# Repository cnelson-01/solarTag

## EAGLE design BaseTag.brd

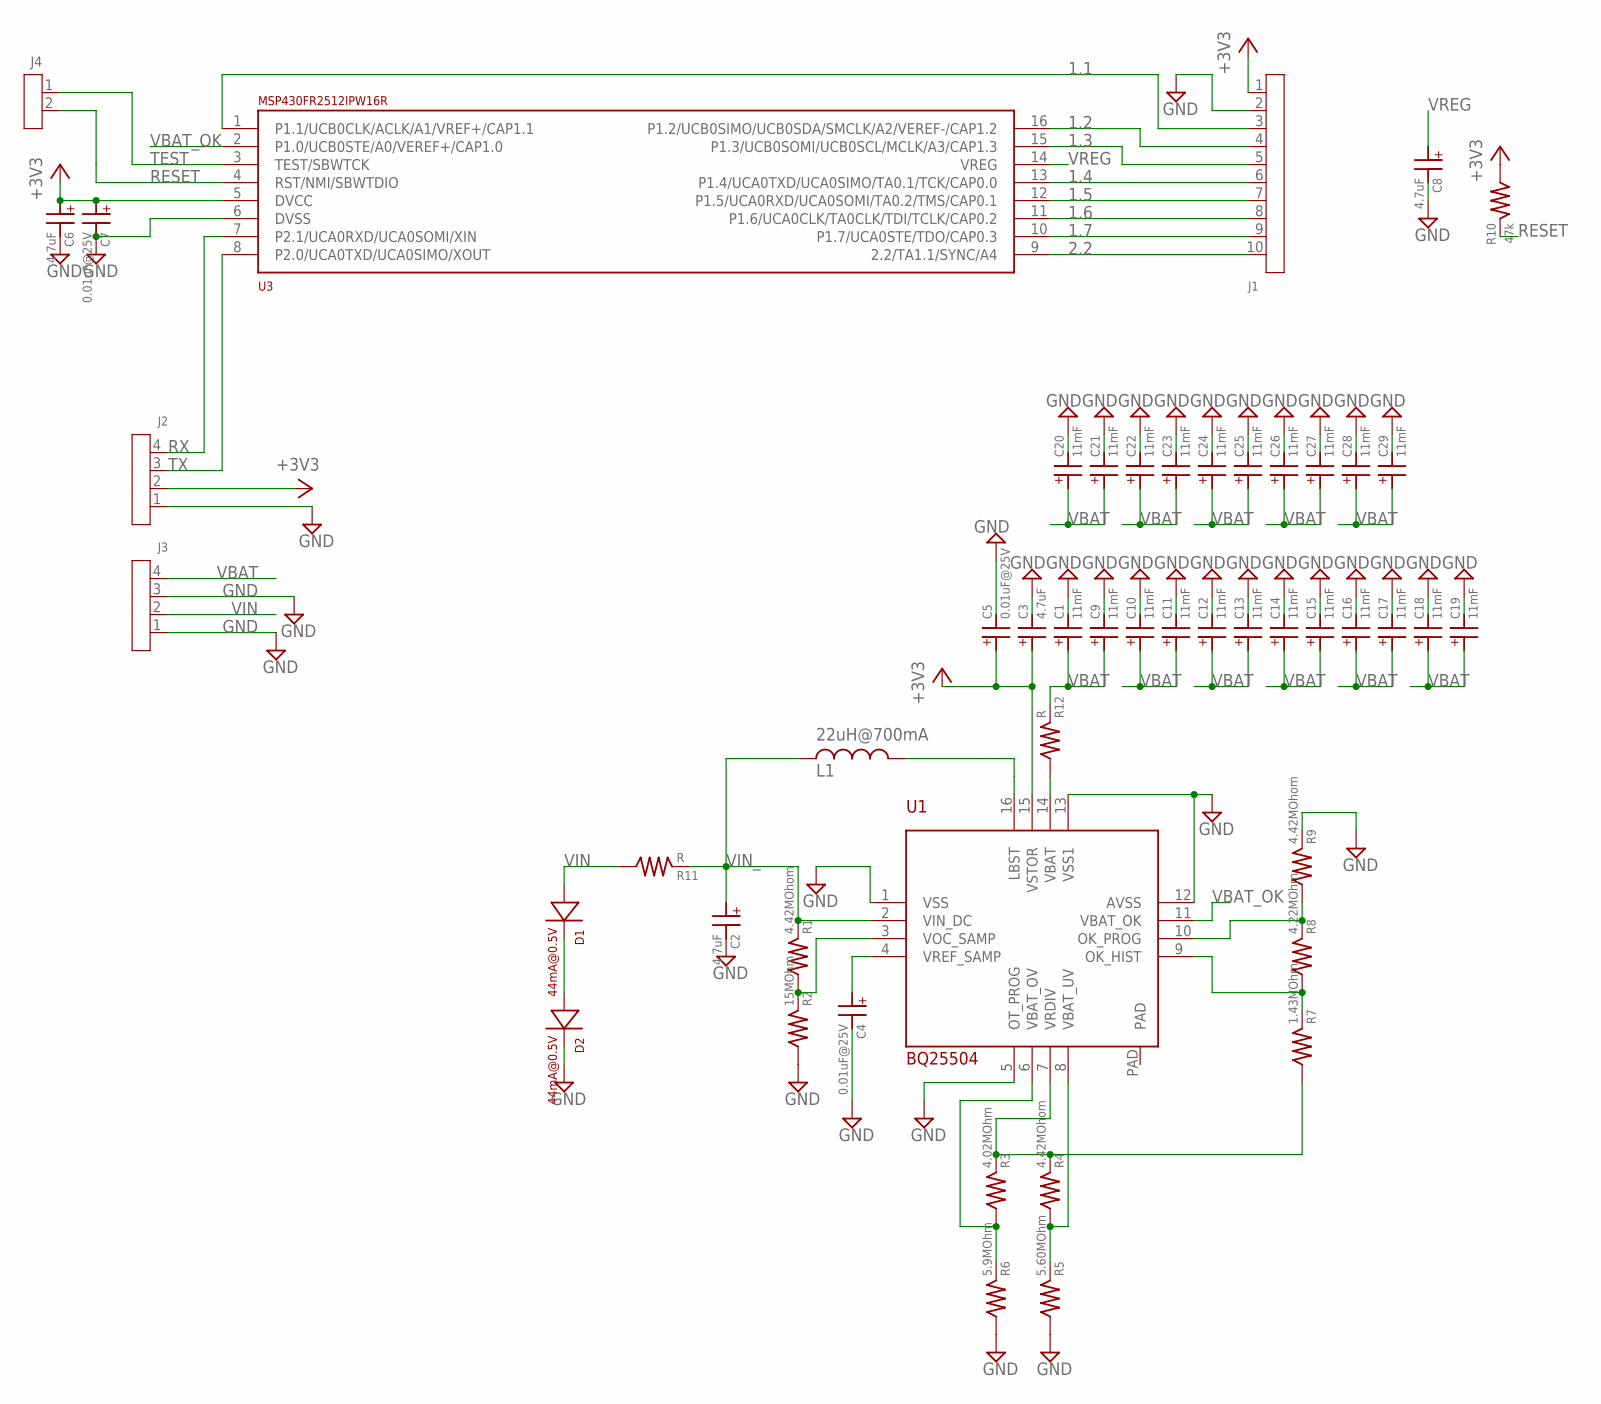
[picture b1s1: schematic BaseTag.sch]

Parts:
C1, C9, C10, C11, C12, C13, C14, C15, C16, C17, C18, C19, C20, C21, C22, C23, C24, C25, C26, C27, C28, C29: 11mF; CPH3225A-2K
C2, C3, C6, C8: 4.7uF; 0603
C4, C5, C7: 0.01uF@25V; 0603
D1, D2: 44mA@0.5V; KXOB22-12X1F
J1: PIN-1-10; PIN-100MIL-1-10
J2, J3: PIN-1-4; PIN-100MIL-1-4
J4: PIN-1-2; PIN-100MIL-1-2
L1: 22uH@700mA; LPS4018-223M
R1, R4, R9: 4.42MOhom; 0603
R2: 15MOhm; 0603
R3: 4.02MOhm; 0603
R5: 5.60MOhm; 0603
R6: 5.9MOhm; 0603
R7: 1.43MOhm; 0603
R8: 4.22MOhm; 0603
R10: 47k; 0603
R11, R12: R; 0603
U1: BQ25504; VQFN-16
U3: MSP430FR2512IPW16RSOIC; SOP65P640X120-16

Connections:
1.1: J1.3, U3.1 (P1.1/UCB0CLK/ACLK/A1/VREF+/CAP1.1)
1.2: J1.4, U3.16 (P1.2/UCB0SIMO/UCB0SDA/SMCLK/A2/VEREF-/C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)
1.3: J1.5, U3.15 (P1.3/UCB0SOMI/UCB0SCL/MCLK/A3/CAP1.3)
1.4: J1.6, U3.13 (P1.4/UCA0TXD/UCA0SIMO/TA0.1/TCK/CAP0.0)
1.5: J1.7, U3.12 (P1.5/UCA0RXD/UCA0SOMI/TA0.2/TMS/CAP0.1)
1.6: J1.8, U3.11 (P1.6/UCA0CLK/TA0CLK/TDI/TCLK/CAP0.2)
1.7: J1.9, U3.10 (P1.7/UCA0STE/TDO/CAP0.3)
2.2: J1.10, U3.9 (2.2/TA1.1/SYNC/A4)
+3V3: C3.+, C5.+, C6.+, C7.+, J1.1, J2.2, R10.+, U1.15 (VSTOR), U3.5 (DVCC)
GND: C1.-, C2.-, C3.-, C4.-, C5.-, C6.-, C7.-, C8.-, C9.-, C10.-, C11.-, C12.-, C13.-, C14.-, C15.-, C16.-, C17.-, C18.-, C19.-, C20.-, C21.-, C22.-, C23.-, C24.-, C25.-, C26.-, C27.-, C28.-, C29.-, D2.-, J1.2, J2.1, J3.1, J3.3, R2.+, R5.+, R6.+, R9.-, U1.1 (VSS), U1.5 (OT_PROG), U1.12 (AVSS), U1.13 (VSS1), U3.6 (DVSS)
unnamed: R1.+, R2.-, U1.3 (VOC_SAMP)
unnamed: R3.-, R4.-, R7.+, U1.7 (VRDIV)
unnamed: R3.+, R6.-, U1.6 (VBAT_OV)
unnamed: R7.-, R8.+, U1.9 (OK_HIST)
unnamed: R4.+, R5.-, U1.8 (VBAT_UV)
unnamed: R8.-, R9.+, U1.10 (OK_PROG)
unnamed: R12.+, U1.14 (VBAT)
unnamed: D1.-, D2.+
unnamed: L1.P$2, U1.16 (LBST)
unnamed: C4.+, U1.4 (VREF_SAMP)
RESET: J4.2, R10.-, U3.4 (RST/NMI/SBWTDIO)
RX: J2.4, U3.7 (P2.1/UCA0RXD/UCA0SOMI/XIN)
TEST: J4.1, U3.3 (TEST/SBWTCK)
TX: J2.3, U3.8 (P2.0/UCA0TXD/UCA0SIMO/XOUT)
VBAT: C1.+, C9.+, C10.+, C11.+, C12.+, C13.+, C14.+, C15.+, C16.+, C17.+, C18.+, C19.+, C20.+, C21.+, C22.+, C23.+, C24.+, C25.+, C26.+, C27.+, C28.+, C29.+, J3.4, R12.-
VBAT_OK: U1.11 (VBAT_OK), U3.2 (P1.0/UCB0STE/A0/VEREF+/CAP1.0)
VIN: D1.+, J3.2, R11.+
VIN_: C2.+, L1.P$1, R1.-, R11.-, U1.2 (VIN_DC)
VREG: C8.+, U3.14 (VREG)

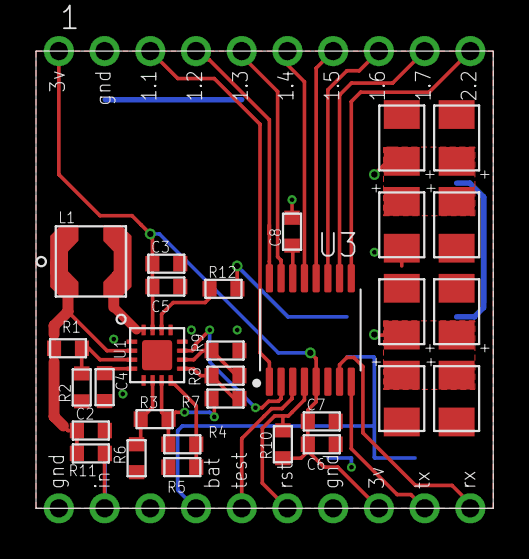
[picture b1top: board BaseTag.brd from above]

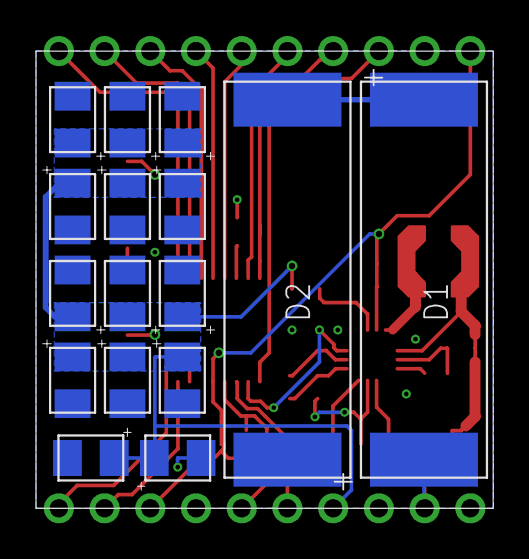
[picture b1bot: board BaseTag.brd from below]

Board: 2 copper layers, 25.4 x 25.4 mm, 50 parts (16 on the bottom side), 29 nets.

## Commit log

2018-07-30 start on prelim layout
2018-08-07 alpha layout
2018-08-07 added simple simulation
2018-08-08 prep for 1" branch
2018-08-09 prelim oneinch
2018-08-09 v1 order
2018-11-18 simulation
    simulation
